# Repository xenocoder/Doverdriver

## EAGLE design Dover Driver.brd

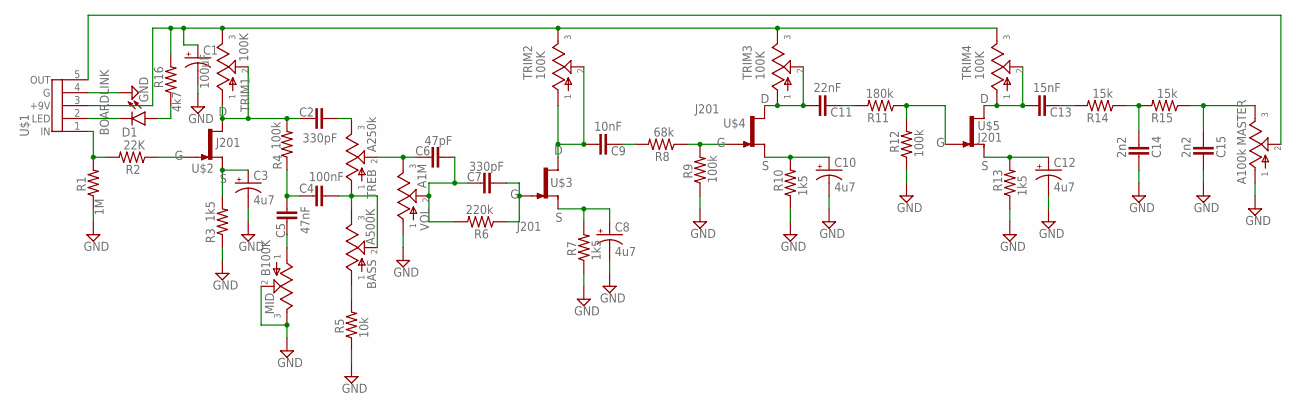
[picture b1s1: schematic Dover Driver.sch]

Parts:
BASS: A500K; 16MM
C1: 100uF; 063_025
C2, C7: 330pF; 050X030_025
C3, C8, C10, C12: 4u7; 050_020_1
C4: 100nF; 075X040
C5: 47nF; 072X025
C6: 47pF; 050X030_025
C9: 10nF; 072X025
C11: 22nF; 072X025
C13: 15nF; 072X025
C14, C15: 2n2; 072X025
D1: LED3MM
MASTER: A100k; 16MM
MID: B100K; 16MM
R1: 1M; R0207/3
R2: 22K; R0207/3
R3, R7, R10, R13: 1k5; R0207/3
R4, R9, R12: 100k; R0207/3
R5: 10k; R0207/3
R6: 220k; R0207/3
R8: 68k; R0207/3
R11: 180k; R0207/3
R14, R15: 15k; R0207/3
R16: 4k7; R0207/3
TREB: A250k; 16MM
TRIM1, TRIM2, TRIM3, TRIM4: 100K; ROUNDTRIM
U$1: BOARDLINK
U$2, U$3, U$4, U$5: J201; SOT23
VOL: A1M; 16MM

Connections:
GND: C1.-, C3.-, C8.-, C10.-, C12.-, C14.2, C15.2, MASTER.1, MID.2, MID.3, R1.1, R3.1, R5.1, R7.1, R9.1, R10.1, R12.1, R13.1, U$1.4 (G), VOL.1
unnamed: R1.2, R2.2, U$1.1 (IN)
unnamed: R2.1, U$2.3 (G)
unnamed: C3.+, R3.2, U$2.2 (S)
unnamed: C2.1, R4.2, TRIM1.1, TRIM1.2, U$2.1 (D)
unnamed: C1.+, R16.2, TRIM1.3, TRIM2.3, TRIM3.3, TRIM4.3, U$1.3 (+9V)
unnamed: C2.2, TREB.3
unnamed: C4.1, C5.2, R4.1
unnamed: C5.1, MID.1
unnamed: BASS.2, BASS.3, C4.2, TREB.1
unnamed: BASS.1, R5.2
unnamed: C6.1, TREB.2, VOL.3
unnamed: C6.2, C7.1, R6.2, VOL.2
unnamed: C7.2, R6.1, U$3.3 (G)
unnamed: C8.+, R7.2, U$3.2 (S)
unnamed: C9.2, TRIM2.1, TRIM2.2, U$3.1 (D)
unnamed: C9.1, R8.2
unnamed: R8.1, R9.2, U$4.3 (G)
unnamed: C11.2, TRIM3.1, TRIM3.2, U$4.1 (D)
unnamed: C10.+, R10.2, U$4.2 (S)
unnamed: C11.1, R11.2
unnamed: R11.1, R12.2, U$5.3 (G)
unnamed: C12.+, R13.2, U$5.2 (S)
unnamed: C13.2, TRIM4.1, TRIM4.2, U$5.1 (D)
unnamed: C15.1, MASTER.3, R15.1
unnamed: C14.1, R14.1, R15.2
unnamed: C13.1, R14.2
unnamed: MASTER.2, U$1.5 (OUT)
unnamed: D1.A, R16.1
unnamed: D1.K (C), U$1.2 (LED)

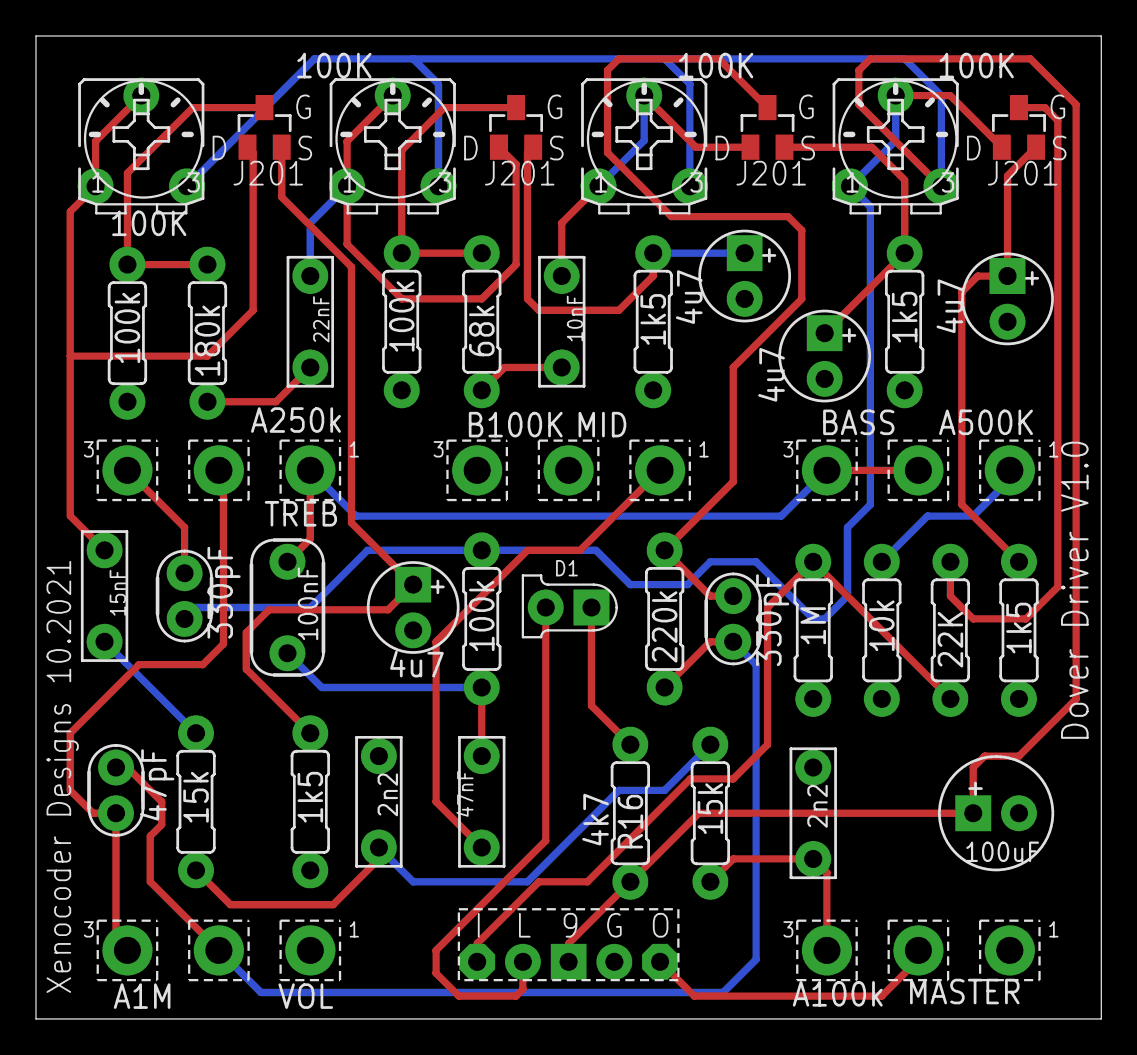
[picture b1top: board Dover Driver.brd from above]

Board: 2 copper layers, 59.2 x 54.6 mm, 46 parts (0 on the bottom side), 30 nets.

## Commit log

2021-10-19 Initial Schematic and 125B layout (not complete)
2021-10-20 Version 1.0 layout finished
2021-10-20 Cleaned up save files
2021-10-22 Drill layout added for version 1.0
